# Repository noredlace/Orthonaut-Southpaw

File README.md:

# Orthonaut-Southpaw
ortho board with southpaw numpad

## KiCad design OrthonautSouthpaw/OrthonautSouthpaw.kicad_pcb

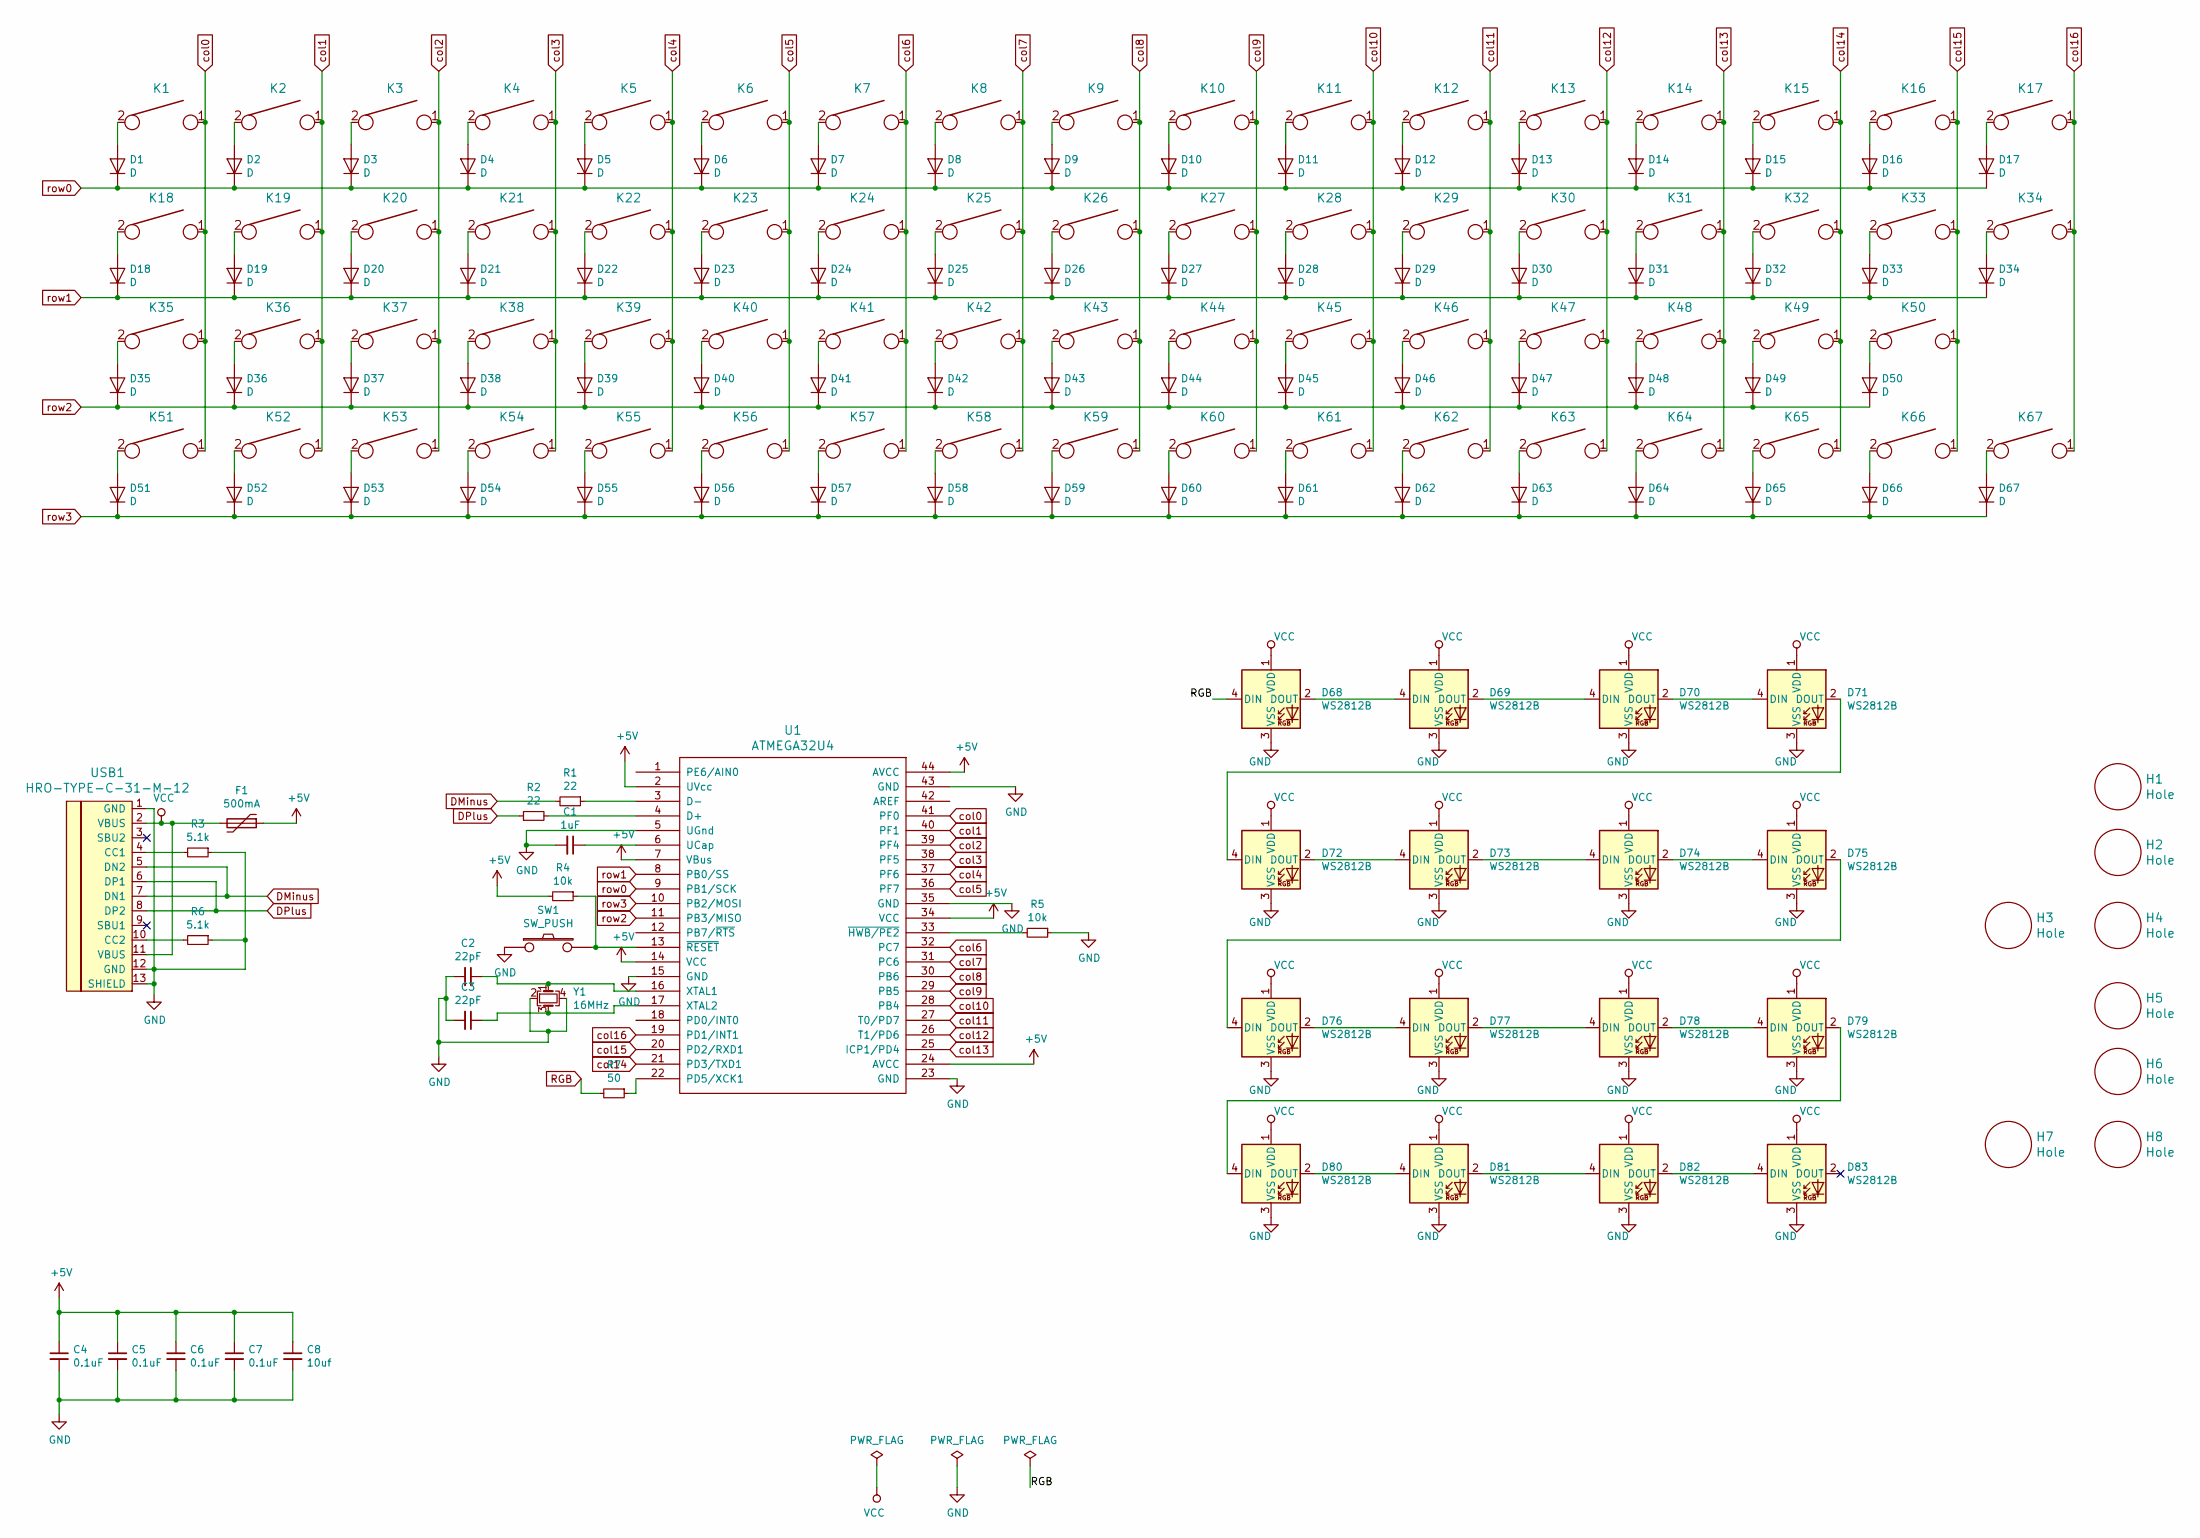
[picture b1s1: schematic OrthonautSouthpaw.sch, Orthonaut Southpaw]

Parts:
C1: 1uF; C_0805
C2, C3: 22pF; C_0805
C4, C5, C6, C7: 0.1uF; C_0805
C8: 10uf; C_0805
D1, D2, D3, D4, D5, D6, D7, D8, D9, D10, D11, D12, D13, D14, D15, D16, D17, D18, D19, D20, D21, D22, D23, D24, D25, D26, D27, D28, D29, D30, D31, D32, D33, D34, D35, D36, D37, D38, D39, D40, D41, D42, D43, D44, D45, D46, D47, D48, D49, D50, D51, D52, D53, D54, D55, D56, D57, D58, D59, D60, D61, D62, D63, D64, D65, D66, D67: D; D_SOD-123
D68, D69, D70, D71, D72, D73, D74, D75, D76, D77, D78, D79, D80, D81, D82, D83: WS2812B; RGBW_LED_5mm
F1: 500mA; Fuse_SMD1206_Reflow
H1, H2, H3, H4, H5, H6, H7, H8: Hole; Poker_oval_hole
K1: 7; MX_PCB_100H
K2: 8; MX_PCB_100H
K3: 9; MX_PCB_100H
K4: Tab; MX_PCB_100H
K5: Q; MX_PCB_100H
K6: W; MX_PCB_100H
K7: E; MX_PCB_100H
K8: R; MX_PCB_100H
K9: T; MX_PCB_100H
K10: Y; MX_PCB_100H
K11: U; MX_PCB_100H
K12: I; MX_PCB_100H
K13: O; MX_PCB_100H
K14: P; MX_PCB_100H
K15: BackSpace; MX_PCB_100H
K16: Insert; MX_PCB_100H
K17: Home; MX_PCB_100H
K18: 4; MX_PCB_100H
K19: 5; MX_PCB_100H
K20: 6; MX_PCB_100H
K21: Esc; MX_PCB_100H
K22: A; MX_PCB_100H
K23: S; MX_PCB_100H
K24: D; MX_PCB_100H
K25: F; MX_PCB_100H
K26: G; MX_PCB_100H
K27: H; MX_PCB_100H
K28: J; MX_PCB_100H
K29: K; MX_PCB_100H
K30: L; MX_PCB_100H
K31: ;; MX_PCB_100H
K32: '; MX_PCB_100H
K33: Delete; MX_PCB_100H
K34: End; MX_PCB_100H
K35: 1; MX_PCB_100H
K36: 2; MX_PCB_100H
K37: 3; MX_PCB_100H
K38: L_Shift; MX_PCB_100H
K39: Z; MX_PCB_100H
K40: X; MX_PCB_100H
K41: C; MX_PCB_100H
K42: V; MX_PCB_100H
K43: B; MX_PCB_100H
K44: N; MX_PCB_100H
K45: M; MX_PCB_100H
K46: ,; MX_PCB_100H
K47, K53: .; MX_PCB_100H
K48: /; MX_PCB_100H
K49: R_Shift; MX_PCB_100H
K50: Up; MX_PCB_100H
K51: 0; MX_PCB_100H
K52: 00; MX_PCB_100H
K54: L_Ctrl; MX_PCB_100H
K55: Win; MX_PCB_100H
K56: L_Alt; MX_PCB_100H
K57: Lower; MX_PCB_100H
K58: Space; MX_PCB_100H
K59: InnerSpace; MX_PCB_100H
K60: InnerEnter; MX_PCB_100H
K61: Enter; MX_PCB_100H
K62: Raise; MX_PCB_100H
K63: R_Alt; MX_PCB_100H
K64: Fn; MX_PCB_100H
K65: Left; MX_PCB_100H
K66: Down; MX_PCB_100H
K67: Right; MX_PCB_100H
R1, R2: 22; R_0805
R3, R6: 5.1k; R_0805
R4, R5: 10k; R_0805
R7: 50; R_0805
SW1: SW_PUSH; SW_TACT_ALPS_SKQGABE010
U1: ATMEGA32U4; ATMEGA32U4-AU
USB1: HRO-TYPE-C-31-M-12; HRO-TYPE-C-31-M-12-Assembly
Y1: 16MHz; Crystal_SMD_3225-4pin_3.2x2.5mm

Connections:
+5V: C4.1, C5.1, C6.1, C7.1, C8.1, F1.1, R4.2, U1.2 (UVcc), U1.7 (VBus), U1.14 (VCC), U1.24 (AVCC), U1.34 (VCC), U1.44 (AVCC)
DMinus: R1.2, USB1.5 (DN2), USB1.7 (DN1)
DPlus: R2.1, USB1.6 (DP1), USB1.8 (DP2)
GND: C1.2, C2.2, C3.2, C4.2, C5.2, C6.2, C7.2, C8.2, D68.3 (VSS), D69.3 (VSS), D70.3 (VSS), D71.3 (VSS), D72.3 (VSS), D73.3 (VSS), D74.3 (VSS), D75.3 (VSS), D76.3 (VSS), D77.3 (VSS), D78.3 (VSS), D79.3 (VSS), D80.3 (VSS), D81.3 (VSS), D82.3 (VSS), D83.3 (VSS), R3.1, R5.1, R6.1, SW1.1, U1.5 (UGnd), U1.15 (GND), U1.23 (GND), U1.35 (GND), U1.43 (GND), USB1.1 (GND), USB1.12 (GND), USB1.13 (SHIELD), Y1.2, Y1.4
unnamed: C1.1, U1.6 (UCap)
unnamed: C2.1, U1.16 (XTAL1), Y1.1
unnamed: C3.1, U1.17 (XTAL2), Y1.3
unnamed: D1.2 (A), K1.2
unnamed: D2.2 (A), K2.2
unnamed: D3.2 (A), K3.2
unnamed: D4.2 (A), K4.2
unnamed: D5.2 (A), K5.2
unnamed: D6.2 (A), K6.2
unnamed: D7.2 (A), K7.2
unnamed: D8.2 (A), K8.2
unnamed: D9.2 (A), K9.2
unnamed: D10.2 (A), K10.2
unnamed: D11.2 (A), K11.2
unnamed: D12.2 (A), K12.2
unnamed: D13.2 (A), K13.2
unnamed: D14.2 (A), K14.2
unnamed: D15.2 (A), K15.2
unnamed: D16.2 (A), K16.2
unnamed: D17.2 (A), K17.2
unnamed: D18.2 (A), K18.2
unnamed: D19.2 (A), K19.2
unnamed: D20.2 (A), K20.2
unnamed: D21.2 (A), K21.2
unnamed: D22.2 (A), K22.2
unnamed: D23.2 (A), K23.2
unnamed: D24.2 (A), K24.2
unnamed: D25.2 (A), K25.2
unnamed: D26.2 (A), K26.2
unnamed: D27.2 (A), K27.2
unnamed: D28.2 (A), K28.2
unnamed: D29.2 (A), K29.2
unnamed: D30.2 (A), K30.2
unnamed: D31.2 (A), K31.2
unnamed: D32.2 (A), K32.2
unnamed: D33.2 (A), K33.2
unnamed: D34.2 (A), K34.2
unnamed: D35.2 (A), K35.2
unnamed: D36.2 (A), K36.2
unnamed: D37.2 (A), K37.2
unnamed: D38.2 (A), K38.2
unnamed: D39.2 (A), K39.2
unnamed: D40.2 (A), K40.2
unnamed: D41.2 (A), K41.2
unnamed: D42.2 (A), K42.2
unnamed: D43.2 (A), K43.2
unnamed: D44.2 (A), K44.2
unnamed: D45.2 (A), K45.2
unnamed: D46.2 (A), K46.2
unnamed: D47.2 (A), K47.2
unnamed: D48.2 (A), K48.2
unnamed: D49.2 (A), K49.2
unnamed: D50.2 (A), K50.2
unnamed: D51.2 (A), K51.2
unnamed: D52.2 (A), K52.2
unnamed: D53.2 (A), K53.2
unnamed: D54.2 (A), K54.2
unnamed: D55.2 (A), K55.2
unnamed: D56.2 (A), K56.2
unnamed: D57.2 (A), K57.2
unnamed: D58.2 (A), K58.2
unnamed: D59.2 (A), K59.2
unnamed: D60.2 (A), K60.2
unnamed: D61.2 (A), K61.2
unnamed: D62.2 (A), K62.2
unnamed: D63.2 (A), K63.2
unnamed: D64.2 (A), K64.2
unnamed: D65.2 (A), K65.2
unnamed: D66.2 (A), K66.2
unnamed: D67.2 (A), K67.2
unnamed: D68.2 (DOUT), D69.4 (DIN)
unnamed: D69.2 (DOUT), D70.4 (DIN)
unnamed: D70.2 (DOUT), D71.4 (DIN)
unnamed: D71.2 (DOUT), D72.4 (DIN)
unnamed: D72.2 (DOUT), D73.4 (DIN)
unnamed: D73.2 (DOUT), D74.4 (DIN)
unnamed: D74.2 (DOUT), D75.4 (DIN)
unnamed: D75.2 (DOUT), D76.4 (DIN)
unnamed: D76.2 (DOUT), D77.4 (DIN)
unnamed: D77.2 (DOUT), D78.4 (DIN)
unnamed: D78.2 (DOUT), D79.4 (DIN)
unnamed: D79.2 (DOUT), D80.4 (DIN)
unnamed: D80.2 (DOUT), D81.4 (DIN)
unnamed: D81.2 (DOUT), D82.4 (DIN)
unnamed: D82.2 (DOUT), D83.4 (DIN)
unnamed: R1.1, U1.3 (D-)
unnamed: R2.2, U1.4 (D+)
unnamed: R3.2, USB1.4 (CC1)
unnamed: R4.1, SW1.2, U1.13 (~RESET)
unnamed: R5.2, U1.33 (~HWB/PE2)
unnamed: R6.2, USB1.10 (CC2)
unnamed: R7.1, U1.22 (PD5/XCK1)
RGB: D68.4 (DIN), R7.2
VCC: D68.1 (VDD), D69.1 (VDD), D70.1 (VDD), D71.1 (VDD), D72.1 (VDD), D73.1 (VDD), D74.1 (VDD), D75.1 (VDD), D76.1 (VDD), D77.1 (VDD), D78.1 (VDD), D79.1 (VDD), D80.1 (VDD), D81.1 (VDD), D82.1 (VDD), D83.1 (VDD), F1.2, USB1.2 (VBUS), USB1.11 (VBUS)
col0: K1.1, K18.1, K35.1, K51.1, U1.41 (PF0)
col1: K2.1, K19.1, K36.1, K52.1, U1.40 (PF1)
col2: K3.1, K20.1, K37.1, K53.1, U1.39 (PF4)
col3: K4.1, K21.1, K38.1, K54.1, U1.38 (PF5)
col4: K5.1, K22.1, K39.1, K55.1, U1.37 (PF6)
col5: K6.1, K23.1, K40.1, K56.1, U1.36 (PF7)
col6: K7.1, K24.1, K41.1, K57.1, U1.32 (PC7)
col7: K8.1, K25.1, K42.1, K58.1, U1.31 (PC6)
col8: K9.1, K26.1, K43.1, K59.1, U1.30 (PB6)
col9: K10.1, K27.1, K44.1, K60.1, U1.29 (PB5)
col10: K11.1, K28.1, K45.1, K61.1, U1.28 (PB4)
col11: K12.1, K29.1, K46.1, K62.1, U1.27 (T0/PD7)
col12: K13.1, K30.1, K47.1, K63.1, U1.26 (T1/PD6)
col13: K14.1, K31.1, K48.1, K64.1, U1.25 (ICP1/PD4)
col14: K15.1, K32.1, K49.1, K65.1, U1.21 (PD3/TXD1)
col15: K16.1, K33.1, K50.1, K66.1, U1.20 (PD2/RXD1)
col16: K17.1, K34.1, K67.1, U1.19 (PD1/INT1)
row0: D1.1 (K), D2.1 (K), D3.1 (K), D4.1 (K), D5.1 (K), D6.1 (K), D7.1 (K), D8.1 (K), D9.1 (K), D10.1 (K), D11.1 (K), D12.1 (K), D13.1 (K), D14.1 (K), D15.1 (K), D16.1 (K), D17.1 (K), U1.9 (PB1/SCK)
row1: D18.1 (K), D19.1 (K), D20.1 (K), D21.1 (K), D22.1 (K), D23.1 (K), D24.1 (K), D25.1 (K), D26.1 (K), D27.1 (K), D28.1 (K), D29.1 (K), D30.1 (K), D31.1 (K), D32.1 (K), D33.1 (K), D34.1 (K), U1.8 (PB0/SS)
row2: D35.1 (K), D36.1 (K), D37.1 (K), D38.1 (K), D39.1 (K), D40.1 (K), D41.1 (K), D42.1 (K), D43.1 (K), D44.1 (K), D45.1 (K), D46.1 (K), D47.1 (K), D48.1 (K), D49.1 (K), D50.1 (K), U1.11 (PB3/MISO)
row3: D51.1 (K), D52.1 (K), D53.1 (K), D54.1 (K), D55.1 (K), D56.1 (K), D57.1 (K), D58.1 (K), D59.1 (K), D60.1 (K), D61.1 (K), D62.1 (K), D63.1 (K), D64.1 (K), D65.1 (K), D66.1 (K), D67.1 (K), U1.10 (PB2/MOSI)

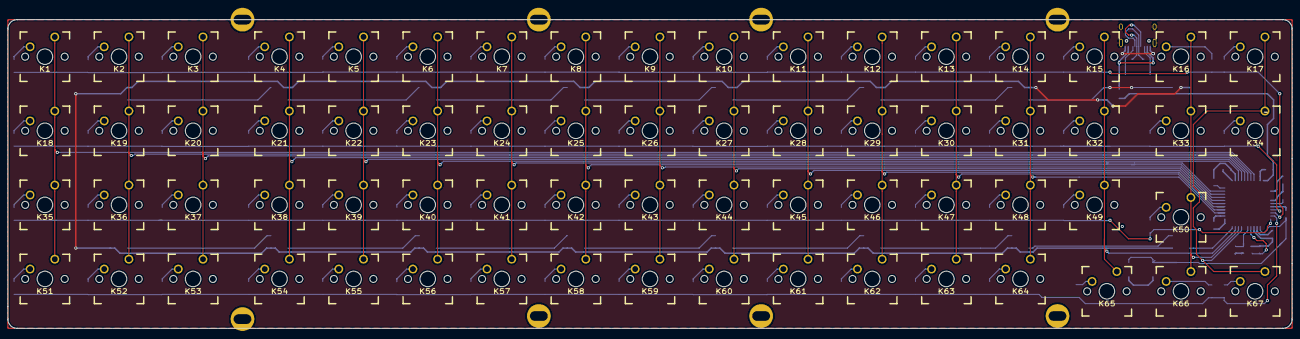
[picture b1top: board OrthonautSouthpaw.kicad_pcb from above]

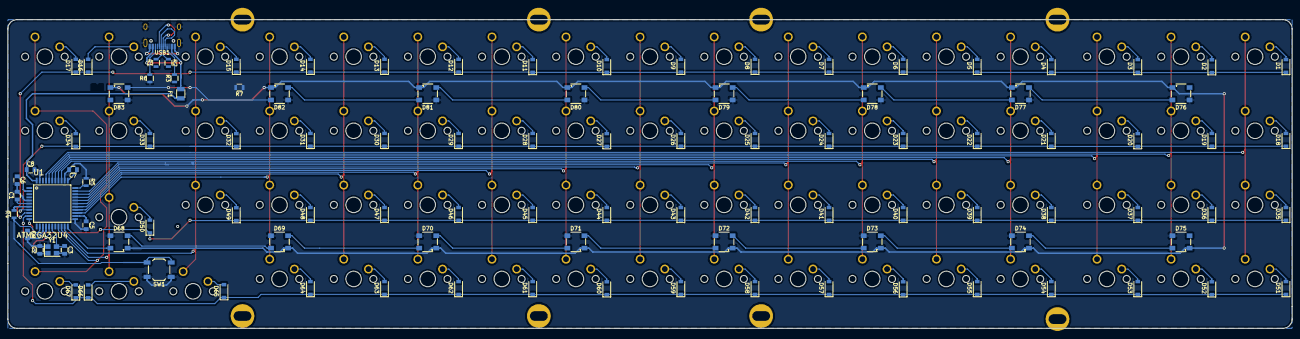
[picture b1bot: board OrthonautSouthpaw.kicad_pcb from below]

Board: 2 copper layers, 330.2 x 79.4 mm, 178 parts (103 on the bottom side), 119 nets.

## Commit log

2019-05-22 update schematic
2019-05-24 finished v1 board designed
2019-05-24 ordered pcb. used swillkb for case design
2019-05-24 fix case files
2019-06-11 update v2
    v2 involves flipping the elitec component and moving it to have more space for the switch. arguably better tracing than v1
2020-02-09 Update fp-info-cache
2020-02-09 update basic readme
2020-02-09 push start to v3
    update to using atmega32u4. modify global libraries to project libraries. looking into type c connections to finish up schematic for atmega
2020-02-09 90% done with smd design
    all smd components traced except for the rgb legs. need to validate the correct pullthrough design for rgb and need to validate the type c connections
